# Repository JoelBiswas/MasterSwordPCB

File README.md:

# MasterSwordPCB
PCB created for Hack Club Solder

Slack Username: Joel Biswas

The PCB is in the shape of a master sword. The button acts as a toggle on/off switch. When the system is on, the potentiometer controls the vibration strength of a motor near the top of the sword. The circuit uses a transistor-based latch design to allow the button to act as a toggle.

Bill of Materials:
Resistor (68k) - 1
Resistor (15k) - 1
Resistor (680) - 1
Resistor (330k) - 1
Resistor (470k) - 1
2N3904 transistor (NPN Type) - 2
Mini Motor Disc - 1
6mm Push Button - 1
Potentiometer - 1
CR2032 battery cell - 1

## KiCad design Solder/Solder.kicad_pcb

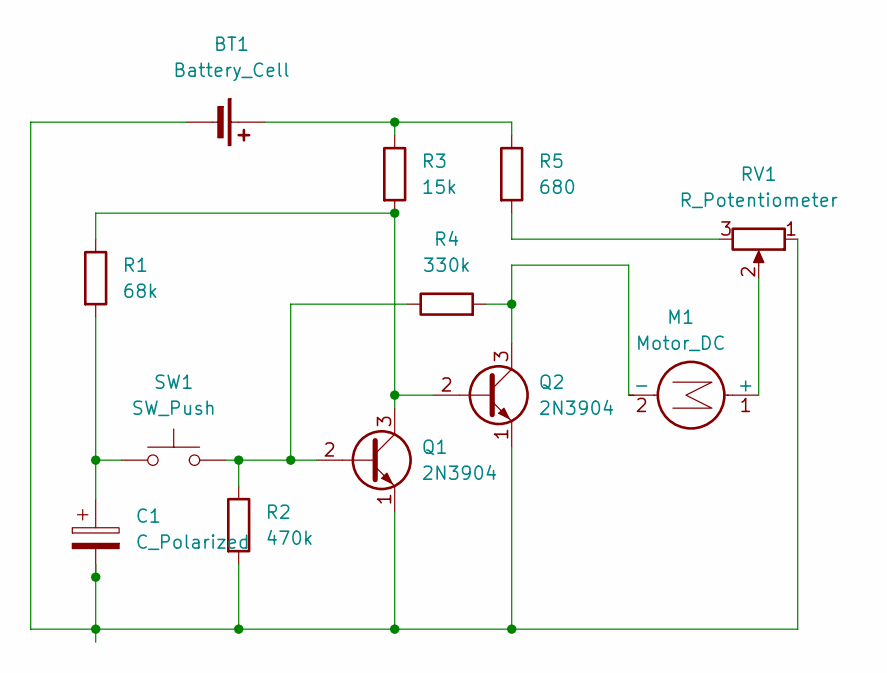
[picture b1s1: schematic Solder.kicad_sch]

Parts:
BT1: Battery_Cell; BatteryHolder_Keystone_3034_1x20mm
C1: C_Polarized; CP_Radial_D8.0mm_P5.00mm
M1: Motor_DC; PinHeader_1x20_P2.54mm_Vertical
Q1, Q2: 2N3904; TO-92_Inline
R1: 68k; R_Axial_DIN0207_L6.3mm_D2.5mm_P7.62mm_Horizontal
R2: 470k; R_Axial_DIN0207_L6.3mm_D2.5mm_P7.62mm_Horizontal
R3: 15k; R_Axial_DIN0207_L6.3mm_D2.5mm_P7.62mm_Horizontal
R4: 330k; R_Axial_DIN0207_L6.3mm_D2.5mm_P7.62mm_Horizontal
R5: 680; R_Axial_DIN0207_L6.3mm_D2.5mm_P7.62mm_Horizontal
RV1: R_Potentiometer; Potentiometer_Vishay_T73YP_Vertical
SW1: SW_Push; SW_PUSH_6mm

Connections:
unnamed: BT1.1 (+), R3.1, R5.1
unnamed: BT1.2 (-), C1.2, Q1.1 (E), Q2.1 (E), R2.2, RV1.1
unnamed: C1.1, R1.2, SW1.1
unnamed: M1.1 (+), RV1.2
unnamed: M1.2 (-), Q2.3 (C), R4.2
unnamed: Q1.2 (B), R2.1, R4.1, SW1.2
unnamed: Q1.3 (C), Q2.2 (B), R1.1, R3.2
unnamed: R5.2, RV1.3

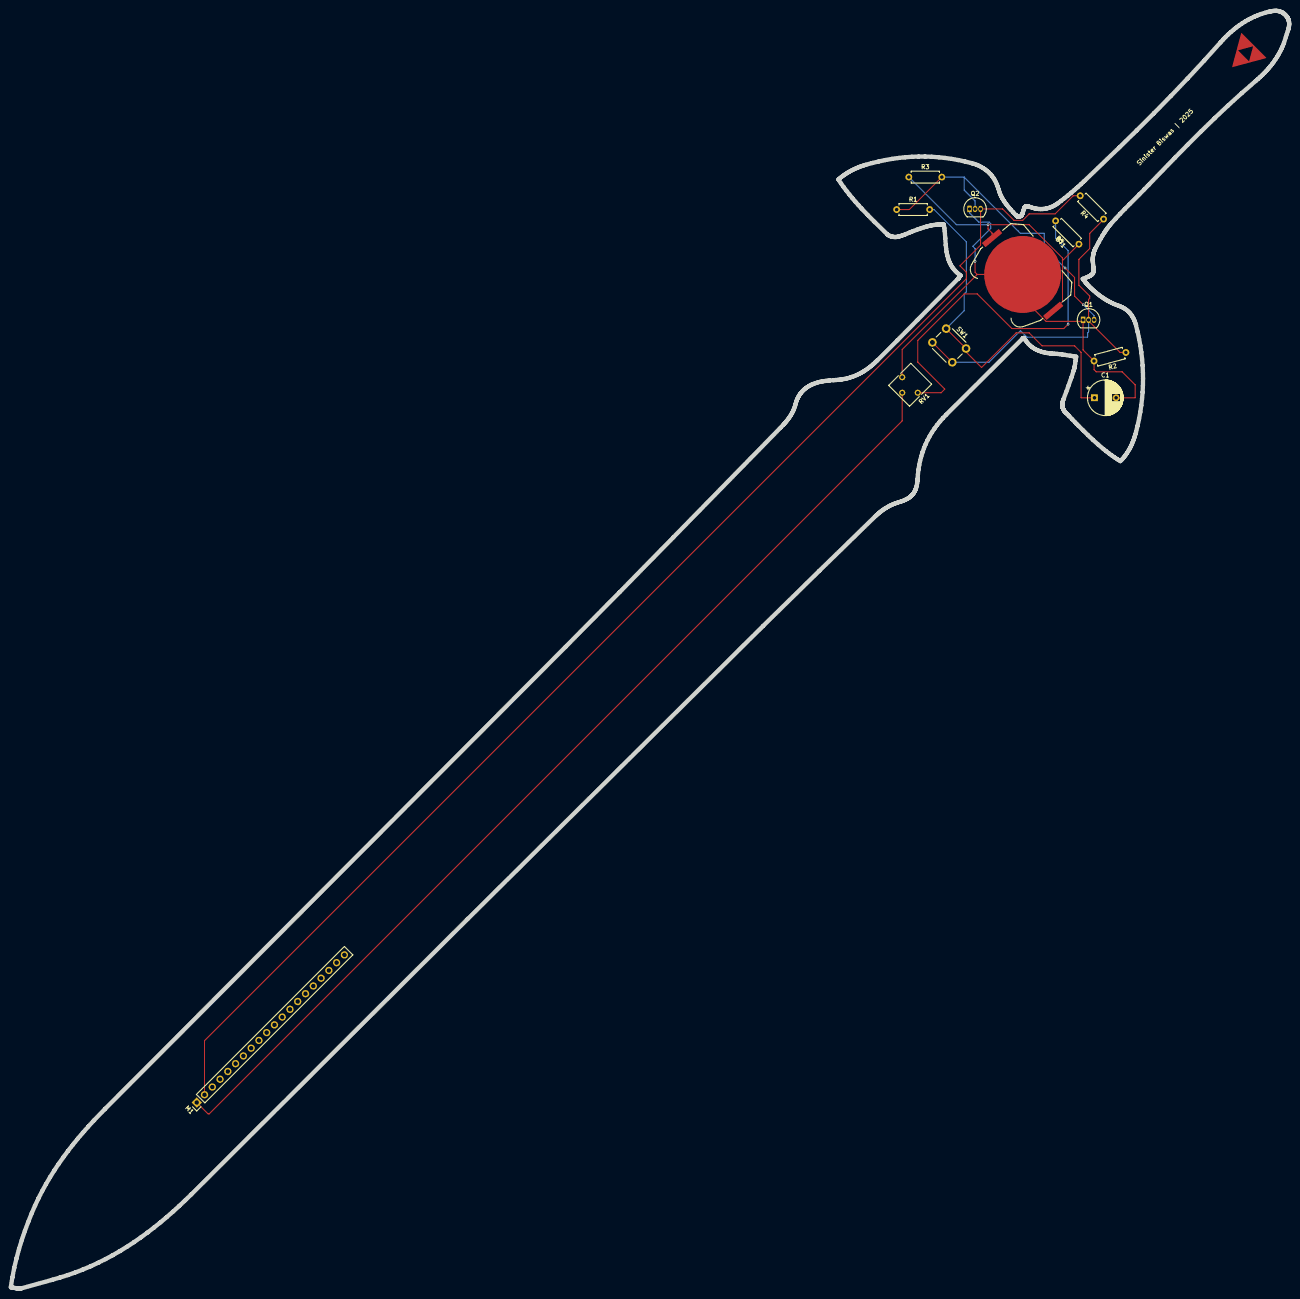
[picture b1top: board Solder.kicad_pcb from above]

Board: 2 copper layers, 295.5 x 295.3 mm, 12 parts (0 on the bottom side), 8 nets.

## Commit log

2025-05-05 Added files
